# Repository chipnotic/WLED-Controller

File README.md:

# WLED-Controller
Controller PCB for WLED, dual strip output, relay power control, option button.

## BOM
```
Ref	Qty	 Value			Datasheet	 													Digikey	 	RS Code
D1	1	1N4007			https://docs.rs-online.com/9d79/0900766b81383fbb.pdf									1N4007-TPMSCT-ND	738-4724
D2	1	STPS10L25D		https://docs.rs-online.com/3abc/0900766b812940ee.pdf									497-2738-5-ND		795-8795
J1-6 	6	0.1" Pinheader 3pin
J7	1	0.2" Screw Terminal 2pin
J7 	1	Screw_Terminal_01x02

Q1	1	BC547			https://rocelec.widen.net/view/pdf/wnpm8l45kj/ONSM-S-A0003590719-1.pdf?t.download=true&u=5oefqw			BC550CBUFS-ND		761-9828
R1	1	4k3			~															A142719CT-ND		148-657
RL1	1	Omron G5LE-1-DC5	https://docs.rs-online.com/ab22/0900766b8132a177.pdf									Z1014-ND		808-8465
U1	1	74125			https://www.ti.com/general/docs/suppproductinfo.tsp?distId=10&gotoUrl=http%3A%2F%2Fwww.ti.com%2Flit%2Fgpn%2Fcd74hc125	296-2089-5-ND		634-596
U2	1	WeMos_D1_mini		https://wiki.wemos.cc/products:d1:d1_mini#documentation	
```

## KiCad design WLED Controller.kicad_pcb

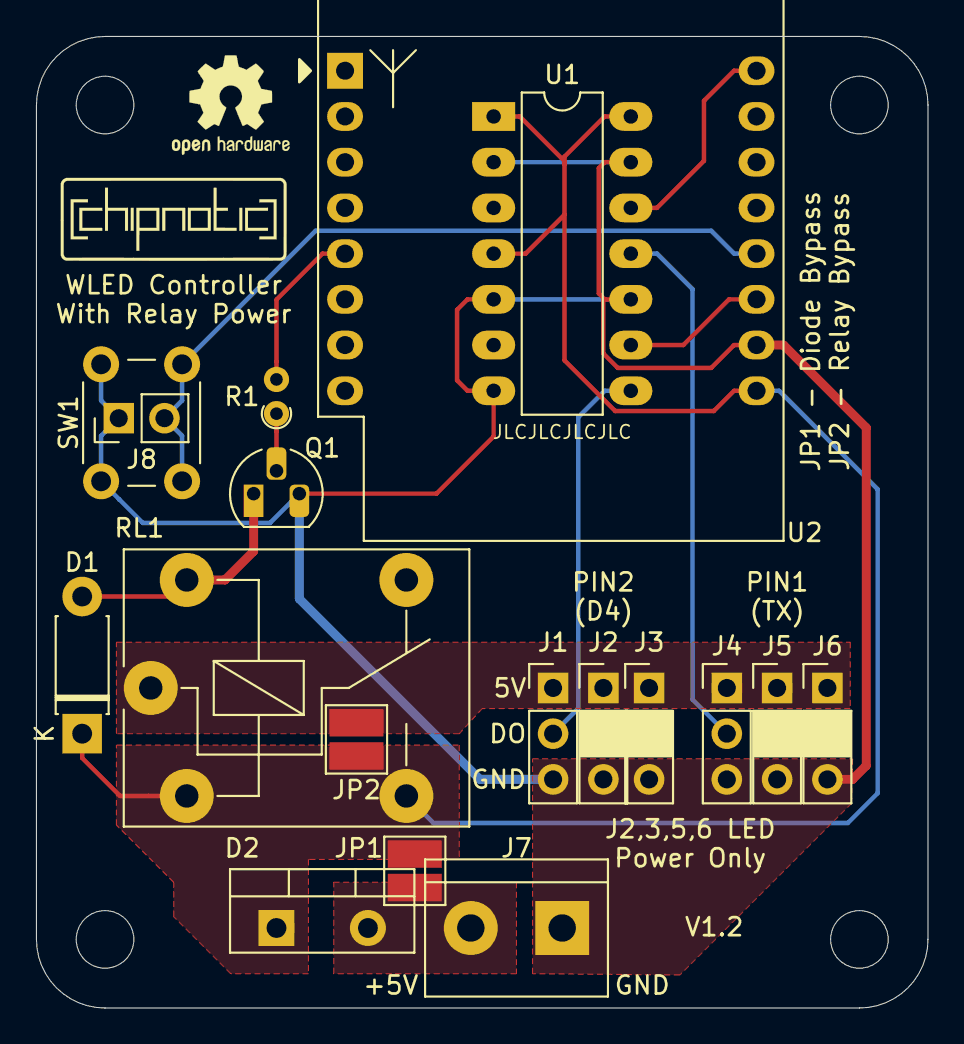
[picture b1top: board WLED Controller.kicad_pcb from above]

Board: 2 copper layers, 49.5 x 54.0 mm, 24 parts (0 on the bottom side), 12 nets.

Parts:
D1: 1N4007; D_DO-41_SOD81_P7.62mm_Horizontal
D2: STPS10L25D; TO-220-2_Vertical
H1, H2, H3, H4: MountingHole; MountingHole_3.2mm_M3
J1, J2, J3, J4, J5, J6: Conn_01x03; PinHeader_1x03_P2.54mm_Vertical
J7: Screw_Terminal_01x02; TerminalBlock_bornier-2_P5.08mm
J8: Conn_01x02; PinHeader_1x02_P2.54mm_Vertical
JP1, JP2: SolderJumper_2_Open; SolderJumper-2_P3mm
Q1: BC547; TO-92L_HandSolder
R1: 4k3; R_Axial_DIN0204_L3.6mm_D1.6mm_P1.90mm_Vertical
RL1: Omron G5LE-1-DC5; Relay_SPDT_Finder_36.11
SW1: SW_Push; SW_PUSH_6mm
SYM1: OSHW Logo; OSHW-Logo2_7.3x6mm_SilkScreen
SYM2: Chipnotic Logo; Chipnotic
U1: 74125; DIP-14_W7.62mm_LongPads
U2: WeMos_D1_mini; WEMOS_D1_mini_light

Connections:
+5V: D1.1, D2.1, JP1.2, JP2.1, RL1.14, RL1.A1, U1.1, U1.4, U1.14, U2.9
GND: J1.3, J2.3, J3.3, J4.3, J5.3, J6.3, J7.1, J8.1, Q1.3, SW1.2, U1.2, U1.5, U1.7, U1.10, U1.13, U2.10
LED1OP: U1.9, U2.11
LED2OP: U1.12, U2.16
LED5V: J1.1, J2.1, J3.1, J4.1, J5.1, J6.1, JP2.2, RL1.11
unnamed: D1.2, Q1.1, RL1.A2
unnamed: D2.2, J7.2, JP1.1
unnamed: J1.2, U1.8
unnamed: J4.2, U1.11
unnamed: J8.2, SW1.1, U2.12
unnamed: Q1.2, R1.1
RELAY: R1.2, U2.5

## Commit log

2021-09-06 First Upload
    Upload of V1.3
2021-09-07 Version V1.2
    Uploaded old version previously
2021-09-07 Update README.md
    Added BOM
2021-09-07 Update README.md
    Remove unnecessary text
2021-09-07 Update README.md
    Update formatting
